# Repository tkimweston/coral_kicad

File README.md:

# coral_kicad
This repository contains the kicad footprint and symbol for the Google Coral Accelerator Module.  
<br>It is a small 10x15mm LGA-120 package.
<br>It is my first attempt commiting kicad library and footprint files to github.  Contact me if you find any issues downloading and using the files.

MIT License
©️ Jae Hyun (Tony) Kim

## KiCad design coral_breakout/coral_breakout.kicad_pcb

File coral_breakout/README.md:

Coral breakout PCB files.
The project only builds a basic breakout with just a decoupling capacitor on VIN.  It can be used to make a specific purpose board like USB or PCI.

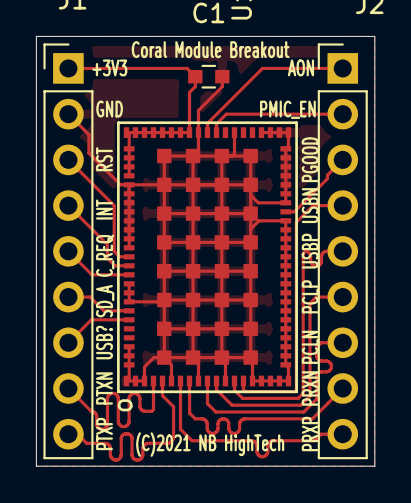
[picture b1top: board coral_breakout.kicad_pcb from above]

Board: 2 copper layers, 18.8 x 23.9 mm, 4 parts (0 on the bottom side), 18 nets.

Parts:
C1: 100nF; C_0603
J1, J2: Conn_01x09_Male; Pin_Header_Straight_1x09_Pitch2.54mm
U1: Coral_1; LGA120

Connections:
+3V3: C1.1, J1.1, U1.56, U1.57, U1.58, U1.59, U1.60, U1.61, U1.62, U1.63, U1.64, U1.65, U1.66, U1.67
/AON: J2.1, U1.54
/CLKREQ_L: J1.5, U1.78
/INTR: J1.4, U1.77
/PCIE_REFCLK_N: J2.7, U1.10
/PCIE_REFCLK_P: J2.6, U1.11
/PCIE_RX_N: J2.8, U1.8
/PCIE_RX_P: J2.9, U1.7
/PCIE_TX_N: J1.8, U1.4
/PCIE_TX_P: J1.9, U1.5
/PGOOD4: J2.3, U1.37
/PMIC_EN: J2.2, U1.53
/RST_L: J1.3, U1.76
/SD_ALARM: J1.6, U1.82
/USB2_D_N: J2.4, U1.14
/USB2_D_P: J2.5, U1.13
/USB_SEL: J1.7, U1.83
GND: C1.2, J1.2, U1.1, U1.2, U1.3, U1.6, U1.9, U1.12, U1.15, U1.16, U1.17, U1.18, U1.19, U1.20, U1.21, U1.22, U1.23, U1.24, U1.25, U1.26, U1.27, U1.28, U1.29, U1.30, U1.31, U1.32, U1.33, U1.34, U1.35, U1.36, U1.38, U1.39, U1.40, U1.41, U1.42, U1.43, U1.44, U1.45, U1.46, U1.47, U1.48, U1.51, U1.55, U1.68, U1.69, U1.70, U1.71, U1.72, U1.73, U1.74, U1.75, U1.79, U1.80, U1.81, U1.86, U1.87, U1.88, U1.89, U1.90, U1.91, U1.92, U1.93, U1.94, U1.95, U1.96, U1.97, U1.98, U1.99, U1.100, U1.101, U1.102, U1.103, U1.104, U1.105, U1.106, U1.107, U1.108, U1.109, U1.110, U1.111, U1.112, U1.113, U1.114, U1.115, U1.116, U1.117, U1.118, U1.119, U1.120

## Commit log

2021-02-16 First upload of the LGA120 footprint
2021-02-16 Coral Accelerator Module symbol
2021-02-17 Add files via upload
    Coral Breakout PCB design in KiCad
2021-02-17 Create README.md
    Initial commit
2021-02-17 Rename readme.md to README.md
2021-02-17 Create LICENSE

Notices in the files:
coral_breakout/coral_breakout.kicad_pcb:
(C)2021 NB HighTech
